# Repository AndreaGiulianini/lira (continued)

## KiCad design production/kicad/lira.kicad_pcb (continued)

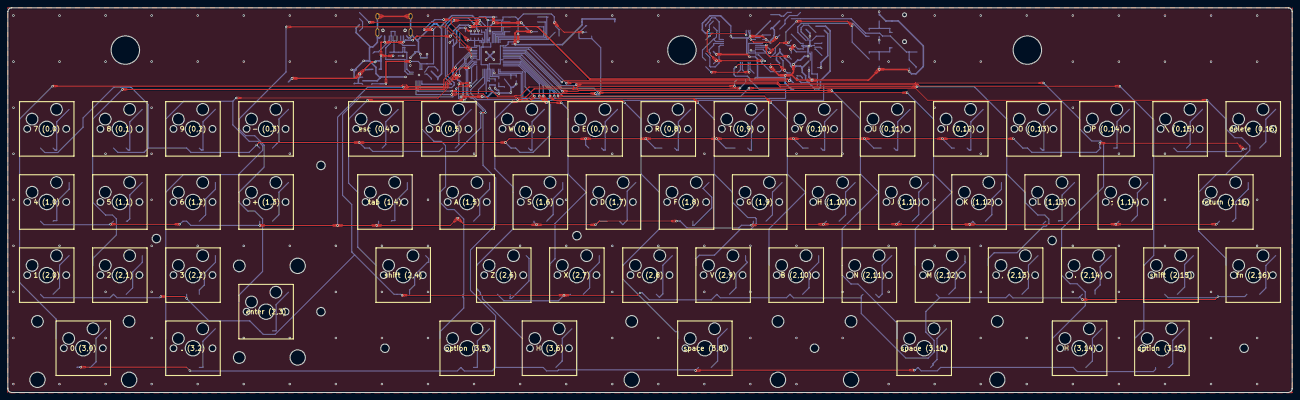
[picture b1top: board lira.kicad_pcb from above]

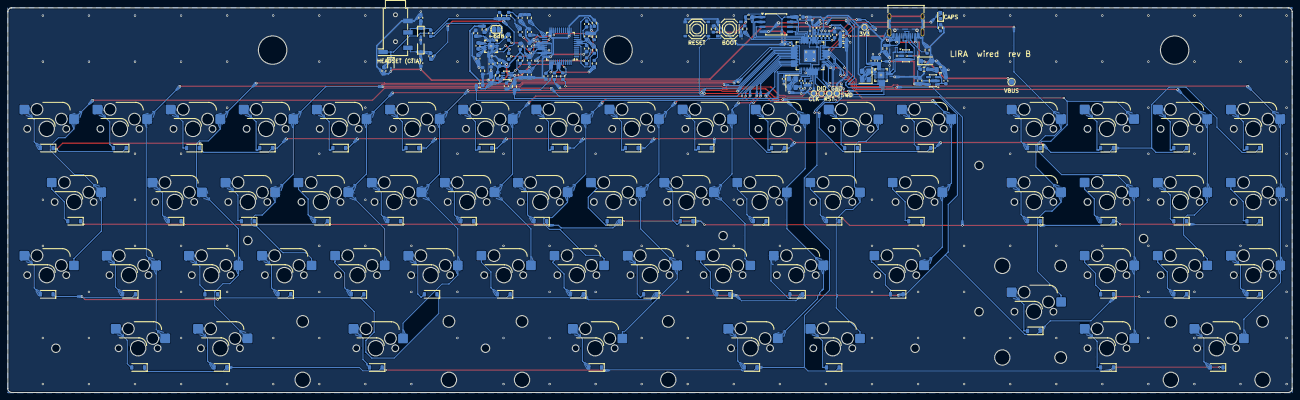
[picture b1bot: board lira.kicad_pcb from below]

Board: 2 copper layers, 334.6 x 100.2 mm, 228 parts (156 on the bottom side), 147 nets.

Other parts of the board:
H1, H2, H3, H4, H5, H6, H7, H8: M2; MountingHole_2.2mm_M2
HB1, HB2, HB3: case bolt; MountingHole_3.2mm_M3
ST37, ST50: stab 2u; Stabilizer_Cherry_MX_2.00u
ST54, ST55: stab 3u; Stabilizer_Cherry_MX_3.00u

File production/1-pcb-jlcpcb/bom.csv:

Comment,Designator,Footprint,LCSC Part #
100nF,"C1,C140,C3,C5,C6,C8,C9",C_0402_1005Metric,C1525
1uF,"C102,C108,C110,C118,C123,C126,C129,C130,C135,C136",C_0603_1608Metric,C15849
4.7uF,"C103,C116,C127",C_0603_1608Metric,C19666
4.7uF,C104,C_0805_2012Metric,C1779
1uF,"C11,C12",C_0402_1005Metric,C52923
100nF,"C112,C114,C115,C117,C119,C15",C_0603_1608Metric,C14663
10uF,"C113,C120,C121,C122",C_0603_1608Metric,C19702
100pF,"C124,C125,C128",C_0603_1608Metric,C14858
15pF,"C13,C14",C_0402_1005Metric,C1548
2.2uF,"C133,C134",C_0603_1608Metric,C23630
10nF,"C138,C139",C_0603_1608Metric,C57112
1nF,C16,C_0603_1608Metric,C1588
1N4148W,"D1,D10,D11,D12,D13,D14,D15,D16,D17,D18,D19,D2,D20,D21,D22,D23,D24,D25,D26,D27,D28,D29,D3,D30,D31,D32,D33,D34,D35,D36,D37,D38,D39,D4,D40,D41,D42,D43,D44,D45,D46,D47,D48,D49,D5,D50,D51,D52,D53,D54,D55,D56,D57,D6,D7,D8,D9",D_SOD-123,C81598
LED red,D103,LED_0603_1608Metric,C2286
PESD5V0,"D105,D106,D107",D_SOD-323,C19224
SMF5.0A,D108,D_SOD-123F,C2857263
USB-C,J1,USB_C_Receptacle_HRO_TYPE-C-31-M-12,C165948
PJ-320D-4A,J3,Jack_3.5mm_KoreanHropartsElec_PJ-320D-4A_Horizontal,C95562
600R@100MHz,"L101,L102,L103,L104",L_0603_1608Metric,C1002
1k,R1,R_0402_1005Metric,C11702
1k,"R107,R116,R118,R3",R_0603_1608Metric,C21190
5.1k,"R108,R109",R_0603_1608Metric,C23186
22,"R110,R111",R_0603_1608Metric,C23345
100k,"R112,R119,R124",R_0603_1608Metric,C25803
1M,R113,R_0603_1608Metric,C22935
1.2k,R114,R_0603_1608Metric,C22765
2.2k,R115,R_0603_1608Metric,C4190
10k,"R120,R121,R122,R123,R2,R4",R_0603_1608Metric,C25804
27,"R5,R6",R_0402_1005Metric,C2909343
1,R7,R_0603_1608Metric,C22936
22k,R8,R_0603_1608Metric,C31850
27k,R9,R_0603_1608Metric,C22967
MX hot-swap socket (Kailh CPG151101S11 type),"S1,S10,S11,S12,S13,S14,S15,S16,S17,S18,S19,S2,S20,S21,S22,S23,S24,S25,S26,S27,S28,S29,S3,S30,S31,S32,S33,S34,S35,S36,S37,S38,S39,S4,S40,S41,S42,S43,S44,S45,S46,S47,S48,S49,S5,S50,S51,S52,S53,S54,S55,S56,S57,S6,S7,S8,S9",Kailh_MX_Hotswap,C41430893
BOOT,"SW101,SW102",SW-SMD_4P-L5.1-W5.1-P3.70-LS6.5-TL_H1.5,C318884
RP2040,U1,QFN-56-1EP_7x7mm_P0.4mm_EP3.2x3.2mm,C2040
W25Q128JVS,U2,SOIC-8_5.3x5.3mm_P1.27mm,C97521
AP2112K-3.3,U3,SOT-23-5,C51118
USBLC6-2SC6,U4,SOT-23-6,C7519
CH334P,U5,WCH_QFN-16-1EP_3x3mm_P0.5mm_EP1.8x1.8mm,C5373042
CM108B,U6,LQFP-48_7x7mm_P0.5mm,C371347
TPA6132A2,U7,WQFN-16-1EP_3x3mm_P0.5mm_EP1.68x1.68mm,C69901
TPS22919,U8,SOT-363_SC-70-6,C2149796
12MHz,Y1,Crystal_SMD_3225-4Pin_3.2x2.5mm,C20625731
12MHz,Y2,Crystal_SMD_3225-4Pin_3.2x2.5mm,C9002

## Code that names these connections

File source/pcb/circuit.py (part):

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# --------------------------------------------------------------------------------------------- Raspberry Pi RP2040
# Pad number -> pin name (RP2040 datasheet 1.4.1, QFN-56; == KiCad's MCU_RaspberryPi:RP2040 symbol).
RP_PINS = {
    1: "IOVDD", 2: "GPIO0", 3: "GPIO1", 4: "GPIO2", 5: "GPIO3", 6: "GPIO4", 7: "GPIO5", 8: "GPIO6", 9: "GPIO7",
    10: "IOVDD", 11: "GPIO8", 12: "GPIO9", 13: "GPIO10", 14: "GPIO11", 15: "GPIO12", 16: "GPIO13", 17: "GPIO14",
    18: "GPIO15", 19: "TESTEN", 20: "XIN", 21: "XOUT", 22: "IOVDD", 23: "DVDD", 24: "SWCLK", 25: "SWDIO", 26: "RUN",
    27: "GPIO16", 28: "GPIO17", 29: "GPIO18", 30: "GPIO19", 31: "GPIO20", 32: "GPIO21", 33: "IOVDD", 34: "GPIO22",
    35: "GPIO23", 36: "GPIO24", 37: "GPIO25", 38: "GPIO26/ADC0", 39: "GPIO27/ADC1", 40: "GPIO28/ADC2",
    41: "GPIO29/ADC3", 42: "IOVDD", 43: "ADC_AVDD", 44: "VREG_VIN", 45: "VREG_VOUT", 46: "USB_DM", 47: "USB_DP",
    48: "USB_VDD", 49: "IOVDD", 50: "DVDD", 51: "QSPI_SD3", 52: "QSPI_SCLK", 53: "QSPI_SD0", 54: "QSPI_SD2",
    55: "QSPI_SD1", 56: "QSPI_SS", 57: "GND",
}
# Pads with a fixed role (net name). The 1.1 V core supply: the internal regulator's output (VREG_VOUT) feeds both
# DVDD pins. TESTEN is grounded (datasheet: "connect to ground"). USB through 27 ohm to the hub's port 3. The sound
# card is switched by two GPIOs in front (GPIO12: its 5 V, GPIO13: the headphone amplifier) and the firmware watches
# VBUS on GPIO29 (ADC3, next to the 3.3 V corner), through a divider.
RP_FIXED = {
    1: "3V3", 10: "3V3", 22: "3V3", 33: "3V3", 42: "3V3", 49: "3V3", 43: "3V3", 44: "3V3", 48: "3V3",
    23: "1V1", 45: "1V1", 50: "1V1", 19: "GND", 57: "GND", 20: "XIN", 21: "XOUT", 24: "SWCLK", 25: "SWDIO",
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

def rp_pin(pad):
    """'GPIO26/ADC0' -> 'PIN_26' (the name RMK and embassy-rp use)."""
    return "PIN_" + RP_PINS[pad].split("/")[0][4:]


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    "also supplies the USB hub (V5 and VDD33 on 3.3 V, CH334 datasheet 6.4), so nothing but the regulator, the sound "
    "card's switch and the protection sits on VBUS.",
    "VBUS protection at the receptacle: SMF5.0A TVS and a 4.7 uF bulk capacitor damped by 1 ohm (hot-plug ringing); "
    "VBUS divider 22k / 27k + 1 nF to GPIO29 (ADC3) for the firmware.",
    "Status LED (red, Caps Lock) on an RP2040 GPIO, through 1k, as on the wireless board.",
    "Test points: SWD (SWCLK, SWDIO, RESET, GND) in one row in front of the RP2040, 3V3 behind it, VBUS; no VBAT / "
    "VIN.",
    "Sound card: the supply switch U8 is on a GPIO (GPIO12) with a 100k pull-down, as on the wireless board; the "
    "headphone amplifier's EN has its own GPIO (GPIO13) through 100k, held low by 1M (the wireless board delays it with "
    "an RC from the switch). The firmware turns the sound card on when the host has configured the keyboard, the "
    "amplifier 0.2 s later, the amplifier off in USB suspend and as soon as VBUS starts to fall.",
]
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        Part("Y1", "12MHz", "Crystal:Crystal_SMD_3225-4Pin_3.2x2.5mm",
             {1: ("1", "XIN"), 2: ("G", "GND"), 3: ("3", "XOUT_X"), 4: ("G", "GND")}, LCSC["xtal_mcu"],
             "Device:Crystal_GND24", note="Abracon ABM8-272-T3: CL 10 pF, ESR <= 50 ohm"),
        c0402("C13", "15pF", LCSC["c15p_0402"], "XIN", "GND", "load: 2 x (10 pF - ~2.5 pF of board and pin)"),
        c0402("C14", "15pF", LCSC["c15p_0402"], "XOUT_X", "GND"),
        r0402("R1", "1k", LCSC["r1k_0402"], "XOUT", "XOUT_X", "limits the crystal's drive level"),
        # --- QSPI flash: W25Q128JV, 16 MB (the boot ROM's default second stage drives it)
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        # damps it (an RC snubber). Total on VBUS: 6.7 uF nominal, under USB's 10 uF.
        Part("D108", "SMF5.0A", "Diode_SMD:D_SOD-123F", {1: ("K", "VBUS"), 2: ("A", "GND")}, LCSC["tvs5v"],
             "Device:D_Zener", note="5 V TVS (200 W), unidirectional, at the receptacle"),
        r0603("R7", "1", LCSC["r1R"], "VBUS", "VBUS_DAMP", "damping of the bulk capacitor (hot-plug ringing)"),
        two("C104", "4.7uF", "Capacitor_SMD:C_0805_2012Metric", LCSC["c4u7_0805"], "VBUS_DAMP", "GND", "Device:C",
            note="VBUS bulk, damped by R7 (25 V X5R: ~3.5 uF left at 5 V)"),
        # --- VBUS sense for the firmware (unplug: amplifier off before the sound card's supply falls): 22k / 27k
        # (5.5 V -> 3.0 V at the ADC), 1 nF against noise (tau 12 us)
        r0603("R8", "22k", LCSC["r22k"], "VBUS", "VBUS_SENSE", "VBUS divider, top"),
        r0603("R9", "27k", LCSC["r27k"], "VBUS_SENSE", "GND", "VBUS divider, bottom: 0.55 x VBUS on GPIO29 (ADC3)"),
        two("C16", "1nF", "Capacitor_SMD:C_0603_1608Metric", LCSC["c1n"], "VBUS_SENSE", "GND", "Device:C",
            note="at the ADC pin"),
        # --- 3.3 V regulator from VBUS (the wireless board's AP2112K, there fed from the power path)
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           10: ("DP1", None), 11: ("DMU", "USB_DN"), 12: ("DPU", "USB_DP"), 13: ("RESET#/CDP", None),
           14: ("PGANG", None), 15: ("V5", "3V3"), 16: ("VDD33", "3V3"), 17: ("GND", "GND")}
    names = {1: "SPDIFO", 2: "DR", 3: "DW", 4: "SK", 5: "CS", 6: "MUTER", 7: "PWRSEL", 8: "DREG18", 9: "DREG33",
             10: "MODE", 11: "NC", 12: "LEDO", 13: "GPIO3", 14: "DVSS", 15: "GPIO4", 16: "SDIN", 17: "ADSCLK",
             18: "MUTEP", 19: "ADLRCK", 20: "ADMCLK", 21: "LEDR", 22: "ADSEL", 23: "TEST", 24: "AVSS", 25: "VBIAS",
             26: "VREF", 27: "MICIN", 28: "NC", 29: "AVDD", 30: "LOL", 31: "LOBS", 32: "LOR", 33: "AVSS", 34: "AVDD",
             35: "DVDD", 36: "DVSS", 37: "AREG36", 38: "MSEL", 39: "VOLUP", 40: "PDSW", 41: "USBDP", 42: "USBDM",
             43: "GPIO1", 44: "SDOUT", 45: "DAMCLK", 46: "DALRCK", 47: "DASCLK", 48: "VOLDN"}
    # the four mode jumpers are strapped to their datasheet-defined levels with 10k on top of the chip's internal
    # pulls: MODE/ADSEL low = headset mode (playback + record) and internal ADC; PWRSEL/MSEL high (to DREG33, so
    # they are only driven while the codec is on) = 100 mA bus-powered and mixer enabled. Every other unlisted pin
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             note="USB audio codec, crystal-free; operating 0-70 C"),
        r0603("R110", "22", LCSC["r22"], "AUD_DP", "CM_DP", "series resistor at the codec's D+"),
        r0603("R111", "22", LCSC["r22"], "AUD_DN", "CM_DN", "series resistor at the codec's D-"),
        # --- the sound card's 5 V: a TPS22919 switched by the RP2040 (GPIO12, AUD_EN), soft start; its pull-down
        # keeps it off while the RP2040 starts and in the boot ROM (QOD through 1k for a slow fall)
        Part("U8", "TPS22919", "Package_TO_SOT_SMD:SOT-363_SC-70-6",
             {1: ("IN", "VBUS"), 2: ("GND", "GND"), 3: ("ON", "AUD_EN"), 4: ("NC", None), 5: ("QOD", "AUD_QOD"),
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        bead("L102", LCSC["bead"], "AUD_5V", "AUD_DVDD", "digital supply filter"),
        c0603("C113", "10uF", LCSC["c10u"], "AUD_5V", "GND", "bulk on the switched 5 V"),
        c0603("C114", "100nF", LCSC["c100n"], "AUD_5V", "GND"),
        c0603("C115", "100nF", LCSC["c100n"], "AUD_DVDD", "GND", "at DVDD (pin 35)"),
        c0603("C116", "4.7uF", LCSC["c4u7"], "AUD_DVDD", "GND"),
        c0603("C117", "100nF", LCSC["c100n"], "AUD_AVDD", "GND", "at AVDD (pin 34), 4.5 mm of track from it"),
        c0402("C140", "100nF", LCSC["c100n_0402"], "AUD_AVDD", "GND", "at AVDD (pin 29), 1 mm from it"),
        c0603("C118", "1uF", LCSC["c1u"], "DREG18", "GND", "1.8 V core regulator"),
        c0603("C119", "100nF", LCSC["c100n"], "DREG33", "GND", "3.3 V I/O regulator"),
        c0603("C120", "10uF", LCSC["c10u"], "AREG36", "GND", "3.6 V analog regulator"),
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             "lira:TPA6132A2", note="headphone amplifier, 25 mW into 16 ohm; gain 0 dB, -6 dB with JP3 closed"),
        c0603("C123", "1uF", LCSC["c1u"], "LOL", "AMP_INL", "left input coupling (19.8k: 8 Hz)"),
        c0603("C126", "1uF", LCSC["c1u"], "LOR", "AMP_INR", "right input coupling"),
        c0603("C133", "2.2uF", LCSC["c2u2"], "AUD_5V", "GND", "amplifier VDD, within 5 mm of the pin"),
        c0603("C134", "2.2uF", LCSC["c2u2"], "AMP_VDDH", "GND", "HPVDD (internal supply, nothing else on it)"),
        c0603("C135", "1uF", LCSC["c1u"], "AMP_VSS", "GND", "HPVSS (charge pump output)"),
        c0603("C136", "1uF", LCSC["c1u"], "AMP_CPP", "AMP_CPN", "charge pump flying capacitor"),
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        Part("JP3", "-6 dB", "Jumper:SolderJumper-2_P1.3mm_Open_RoundedPad1.0x1.5mm",
             {1: ("A", "AMP_G0"), 2: ("B", "GND")}, symbol="Jumper:SolderJumper_2_Open",
             note="closed: amplifier gain -6 dB, for very sensitive earphones"),
        # amplifier enable from the RP2040 (GPIO13, AMP_ON): on after the sound card's supply has settled, off first
        # when VBUS starts to fall or the host suspends. 100k in series: EN never pushes current into an unpowered
        # amplifier (EN must stay below VDD + 0.3 V); 1M holds it low while the RP2040 starts (EN: 3.0 V when on)
        r0603("R124", "100k", LCSC["r100k"], "AMP_ON", "AMP_EN", "series: limits EN current when VDD is off"),
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
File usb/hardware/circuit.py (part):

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# --------------------------------------------------------------------------------------------- RP2040

RP2040_PINS = {
    1: "IOVDD", 2: "GPIO0", 3: "GPIO1", 4: "GPIO2", 5: "GPIO3", 6: "GPIO4", 7: "GPIO5", 8: "GPIO6",
    9: "GPIO7", 10: "IOVDD", 11: "GPIO8", 12: "GPIO9", 13: "GPIO10", 14: "GPIO11", 15: "GPIO12",
    16: "GPIO13", 17: "GPIO14", 18: "GPIO15", 19: "TESTEN", 20: "XIN", 21: "XOUT", 22: "IOVDD",
    23: "DVDD", 24: "SWCLK", 25: "SWDIO", 26: "RUN", 27: "GPIO16", 28: "GPIO17", 29: "GPIO18",
    30: "GPIO19", 31: "GPIO20", 32: "GPIO21", 33: "IOVDD", 34: "GPIO22", 35: "GPIO23", 36: "GPIO24",
    37: "GPIO25", 38: "GPIO26/ADC0", 39: "GPIO27/ADC1", 40: "GPIO28/ADC2", 41: "GPIO29/ADC3",
    42: "IOVDD", 43: "ADC_AVDD", 44: "VREG_VIN", 45: "VREG_VOUT", 46: "USB_DM", 47: "USB_DP",
    48: "USB_VDD", 49: "IOVDD", 50: "DVDD", 51: "QSPI_SD3", 52: "QSPI_SCLK", 53: "QSPI_SD0",
    54: "QSPI_SD2", 55: "QSPI_SD1", 56: "QSPI_SS", 57: "GND",
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def rp2040(gpio=None, status_led=37):
    """RP2040 minimum design + USB-C + 3.3 V LDO. gpio: {pad: net} for the matrix lines."""
    gpio = dict(gpio or {})
    gpio.setdefault(status_led, "LED_RED")
    u1 = {pad: (name, gpio.get(pad, RP_FIXED.get(pad))) for pad, name in RP2040_PINS.items()}
    parts = [
        Part("U1", "RP2040", "Package_DFN_QFN:QFN-56-1EP_7x7mm_P0.4mm_EP3.2x3.2mm", u1, LCSC["rp2040"],
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             {1: ("1", "XIN"), 2: ("G", "GND"), 3: ("3", "XOUT_C"), 4: ("G", "GND")}, LCSC["xtal12"],
             "Device:Crystal_GND24", note="Abracon ABM8-272-T3, CL 10 pF; load caps chosen for it"),
        c0603("C13", "15pF", LCSC["c15p"], "XIN", "GND", "CL: 15 pF + ~3 pF stray = 10 pF"), c0603("C14", "15pF", LCSC["c15p"], "XOUT_C", "GND"),
        r0603("R01", "1k", LCSC["r1k"], "XOUT_C", "XOUT", "series damping (RP2040 HDG R5)"),
        Part("U2", "W25Q128JVS", "Package_SO:SOIC-8_3.9x4.9mm_P1.27mm",
             {1: ("CS", "QSPI_SS"), 2: ("DO/IO1", "QSPI_SD1"), 3: ("WP/IO2", "QSPI_SD2"), 4: ("GND", "GND"),
              5: ("DI/IO0", "QSPI_SD0"), 6: ("CLK", "QSPI_SCLK"), 7: ("HOLD/IO3", "QSPI_SD3"), 8: ("VCC", "3V3")},
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           13: ("RESET#/CDP", None), 14: ("PGANG", None), 15: ("V5", "VBUS"), 16: ("VDD33", "HUB_3V3"),
           17: ("GND", "GND")}
    names = {1: "SPDIFO", 2: "DR", 3: "DW", 4: "SK", 5: "CS", 6: "MUTER", 7: "PWRSEL", 8: "DREG18",
             9: "DREG33", 10: "MODE", 11: "NC", 12: "LEDO", 13: "GPIO3", 14: "DVSS", 15: "GPIO4",
             16: "SDIN", 17: "ADSCLK", 18: "MUTEP", 19: "ADLRCK", 20: "ADMCLK", 21: "LEDR", 22: "ADSEL",
             23: "TEST", 24: "AVSS", 25: "VBIAS", 26: "VREF", 27: "MICIN", 28: "NC", 29: "AVDD", 30: "LOL",
             31: "LOBS", 32: "LOR", 33: "AVSS", 34: "AVDD", 35: "DVDD", 36: "DVSS", 37: "AREG36",
             38: "MSEL", 39: "VOLUP", 40: "PDSW", 41: "USBDP", 42: "USBDM", 43: "GPIO1", 44: "SDOUT",
             45: "DAMCLK", 46: "DALRCK", 47: "DASCLK", 48: "VOLDN"}
    nets = {7: "CM_PWRSEL", 8: "DREG18", 9: "DREG33", 10: "CM_MODE", 14: "GND", 22: "CM_ADSEL", 23: "GND",
            24: "GND", 25: "VBIAS", 26: "VREF", 27: "MICIN", 29: "AUD_AVDD", 30: "LOL", 31: "LOBS",
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

def default_gpio():
    """Placeholder matrix pin map so the netlist is complete: COL0..16 -> GPIO0..16, ROW0..3 ->
    GPIO17..20. The real map is chosen from the layout geometry (as Lira's pcb/electronics.py does)
    so the fan-out does not cross itself."""
    pads = [2, 3, 4, 5, 6, 7, 8, 9, 11, 12, 13, 14, 15, 16, 17, 18, 27]  # GPIO0..16
    m = {pads[c]: "COL%d" % c for c in range(17)}
    for r in range(4):
        m[28 + r] = "ROW%d" % r  # GPIO17..20
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
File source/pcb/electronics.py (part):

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        # the side supply pins: IOVDD 1 (right, back end) beside its pin, at the top edge of the matrix lines' fan;
        # IOVDD 10 and 33, in the middle of the fan, are tied to 1 and 42 inside the package, under it
        "C1": (m + 5.2, c - 3.05, 0),
        # in front: the I/O and core capacitors under pins 22 / 23; the 12 MHz crystal to the right, XIN to its
        # top-right pad (with its 15 pF beside it), XOUT through the 1k down its left side to the bottom-left pad
        "C9": (m - 0.1, c + FRONT, 270), "C3": (m + 1.35, c + FRONT, 270),
        "Y1": (m + 4.6, c + 7.1, 270), "R1": (m + 2.3, c + 6.5, 270), "C14": (m + 2.3, c + 8.5, 270),
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        "TP2": (m - 1.0, c + SWD_Y, 0), "TP1": (m - 1.0 - SWD_PITCH, c + SWD_Y, 0),
        "TP5": (m - 1.0 - 2 * SWD_PITCH, c + SWD_Y, 0), "TP4": (m - 1.0 - 3 * SWD_PITCH, c + SWD_Y, 0),
        "TP3": (m - 14.2, c - 7.4, 0),
        # VBUS divider for the firmware (GPIO29, pin 41) and its 1 nF, left of the 3.3 V corner
        "C16": (m - 8.7, c - 2.7, 180), "R9": (m - 8.7, c - 4.3, 180), "R8": (m - 8.7, c - 5.9, 0),
        # BOOT and RESET buttons right of the flash (BOOT under the case's paperclip hole), the BOOT resistor and
        # the RUN pull-up next to them
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        "U7": (m, top + 10.0, 0),
        "JP3": (m - 1.4, top + 5.6, 0), "R112": (m + 1.8, top + 5.6, 270), "C135": (m + 4.0, top + 6.6, 90),
        "C136": (m + 3.4, top + 9.9, 90), "C134": (m + 3.4, top + 13.2, 270), "C133": (m, top + 14.6, 270),
        # amplifier enable from GPIO13: 1M pull-down at EN, 100k in series from the GPIO line, just outside the
        # top-layer keep-out over the amplifier (so the GPIO line can arrive on either layer)
        "R113": (m + 2.2, top + 16.4, 90), "R124": (m + 3.0, top + 20.2, 180),
        # supply switch (VBUS -> AUD_5V) with its input capacitor and its ON pull-down, AUD_5V bulk
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    sgnd = pad_xy(u7, 15)[0]
    xs = x14 + math.copysign(0.1, x14 - sgnd)  # 0.1 mm further from the SGND via
    path(B, "AUD_5V", [(x14, y14), (x14, y14 + 0.5), (xs, y14 + 0.6), (xs, yc - 0.2)], width=0.25)
    # the amplifier's EN (pin 13) down beside C133 into its 1M pull-down and on into the 100k from GPIO13, just outside
    # the keep-out below
    x13, y13 = pad_xy(u7, 13)
    r113, r124 = pad_xy(placed["R113"], 1), pad_xy(placed["R124"], 2)
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
def rp2040_crystal(B, placed):
    """The 12 MHz crystal, drawn here (Hardware design with RP2040 2.3: keep it short): XIN and XOUT leave the
    package's front side together and turn right, under the two GPIO lines that switch the sound card; XIN runs to
    the crystal's top-right pad and on to its 15 pF; XOUT turns down left of the crystal into the 1k, and from it the
    crystal's side (XOUT_X) goes to the 15 pF below and into the bottom-left pad. The crystal's two ground pads are
    joined under it; each ground pad and capacitor has a via into the top layer's plane, whole under all of this."""
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    # it and run side by side along the bottom of the strip (in front of the SWD pads, behind the top row's sockets)
    # to their resistors at the sound card: 70-80 mm that the autorouter, among the matrix lines, does not reliably find
    ends = {"AUD_EN": pad_xy(placed["R119"], 1), "AMP_ON": pad_xy(placed["R124"], 1)}
    for k, (pin, net) in enumerate(((15, "AUD_EN"), (16, "AMP_ON"))):
        x, y = pad_xy(u1, pin)
        y_run = y + 0.76 + 0.4 * k
        x_down = c13[0] + 1.7 - 0.4 * k
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

def vbus_sense(B, placed):
    """GPIO29 (pin 41) left to the divider: the 1 nF, the lower and the upper resistor share one vertical line."""
    u1 = placed["U1"]
    x41, y41 = pad_xy(u1, 41)
    c16, r9, r8 = pad_xy(placed["C16"], 1), pad_xy(placed["R9"], 1), pad_xy(placed["R8"], 2)
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    the 100 pF and the microphone's clamp each have their own."""
    j3 = placed["J3"]
    contact = {p.GetNumber(): pad_xy(j3, p.GetNumber()) for p in j3.Pads() if p.GetNumber()}
    for net, bead, clamp, cap, pin in (("HP_R", "L104", "D106", "C125", "R1"), ("HP_L", "L103", "D105", "C124", "T")):
        b2 = pad_xy(placed[bead], 2)
        d1 = pad_xy(placed[clamp], 1)
        c1 = pad_xy(placed[cap], 1)
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    them up from there already untangled, on either layer."""
    u5 = placed["U5"]
    x_end = X_MCU - 10.0
    for k, (net, pin) in enumerate((("MCU_DN", 5), ("MCU_DP", 6), ("AUD_DN", 7), ("AUD_DP", 8))):
        x, y = pad_xy(u5, pin)
        y_run = y + 0.9 + 0.9 * k
        path(B, net, [(x, y), (x, y_run), (x_end, y_run)])
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    rows = [rp_pin(mapping["ROW%d" % r]) for r in range(n_rows)]
    cols = [rp_pin(mapping["COL%d" % c]) for c in range(n_cols)]
    gpio = {str(pad): net for net, pad in mapping.items()}
    return rows, cols, rp_pin(mapping["LED_RED"]), gpio


def gnd_via(B, fp, reach=0.95):
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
